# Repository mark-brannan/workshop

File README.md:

# workshop
My home workshop stuff.

Rules for the agent are in `AGENTS.md` (not here!)

Machines are in `equipment.md`

## Layout

| Path | What |
|---|---|
| `src/shop/` | Helpers: export every format at once, headless PNG render, test loader |
| `projects/<slug>/` | One part each: `README.md`, `model.py` or `model.scad`, `test_model.py`, `out/` |
| `fusion/` | Fusion 360 scripts, run inside Fusion |
| `projects/calibration/` | First real project: fit numbers for the printer and laser |
| `.github/workflows/build.yml` | Tests and builds every Python model on push |

## Setup

    ~/workshop/setup.sh     # puts `shop` on PATH; yadm bootstrap runs it

Then `shop build`, `shop doctor` (which tools this box has), `shop fusion`
(the folder to add in Fusion's Scripts panel) from any directory.

## Commands

[`RUNBOOK.md`](RUNBOOK.md) is every `shop` command by task, printing included.

    uv sync
    uv run python -m shop.build                      # every project, .py and .scad alike
    uv run python -m shop.build projects/esp32-freenove-universal-mount  # one project
    uv run pytest -q
    shop views projects/<slug>/model.scad <view>   # six labelled OpenSCAD views, montaged into out/

`.scad` models build through whatever OpenSCAD the box has (`src/shop/scad.py`);
on WSL the Windows Nightly is preferred when installed. `projects/README-ab.md` is the measured
OpenSCAD vs build123d comparison on two demo parts (since removed; see git history).

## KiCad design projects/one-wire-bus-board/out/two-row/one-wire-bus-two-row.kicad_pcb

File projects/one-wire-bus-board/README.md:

# One-wire bus board

Symphony: [`firmware/halmet/src/halmet_onewire.h`](https://github.com/mark-brannan/symphony/tree/main/firmware/halmet/src/halmet_onewire.h), [`reference/halmet_firmware.md`](https://github.com/mark-brannan/symphony/tree/main/reference/halmet_firmware.md)

Purpose: tie seven 3-pin screw terminals, each [G D V] in a row, into three nets
(GND, DATA, VCC) with no jumpers and no insulated wire. Six field terminals and a
MASTER whose cable goes to the microcontroller. Any 3-position 2.54 mm screw block, on the front edge, wire entry facing out. Pins are 2.54 mm apart inside a block and 8.2 mm pitch across blocks: the ZPWAN AM128-2.54 body is 8.1 wide by the maker's diagram (7.3-7.8 by calipers), so blocks cannot butt at 3 x 2.54 = 7.62.

Two copper layers, plated pads, no vias: G on top behind the pin row, V on top in front
of it (under the terminal body), D on the bottom between the pin row and G, so D passes under the G stubs.
Hand-built equivalent on a one-sided pad board: bare wire for G and V on the solder
side, one bare wire for D on the top face dipping through each D hole.

R1 is an optional 4.7 k pull-up spot, DATA to VCC, past MASTER: leave it empty when the master has its own.

Outputs in `out/one-row/` (the other forms each have their own folder under `out/`): `one-wire-bus-one-row.kicad_pcb` (KiCad 7 text, generated by `model.py`),
`one-wire-bus-one-row.png` (both layers), and `fab/` (below). Board 76.0 x 10.8 mm, two M3 holes 70 mm apart, each
clear of a 7 mm washer. The same pin grid works on a 2.54 mm perfboard.

Ordering, prices and OSH Park's rules: [oshpark.md](oshpark.md).

## Guessed, not measured

| Value | Now | Why |
|---|---|---|
| Pad / drill | 1.9 / 1.3 mm | commodity 2.54 mm screw block (KF2.54-3P class) |
| Body depth, pin setback | 6.5; 3.3 from the front | commodity 2.54 mm screw block; any in-stock 3P part fits |
| Track width, min clearance | DATA 0.5, GND and VCC 1.0 / 0.3 mm | fab-safe defaults; OSH Park's floor is 0.15 |
| R1 pads | 7.62 pitch, 0.8 drill | fits a 1/4 W axial resistor, body up to 6.3 x 2.5 |
| Terminal pin order | G, D, V, left to right with the wire entry facing you | owner's brief |
| Board lip past the body front | 0.5 mm | keeps copper off the edge |

Blocks sit 8.2 mm apart (`block_pitch`): clear of the 8.1 mm diagram width.

## Four forms: which one to order

The same circuit in four shapes. Each is complete: board file, Gerber zip, KiCad rule check clean against OSH Park's limits.
`model.py` builds the one-row board, `layouts.py` the other three.

| | One-row | Two-row | Ring | Pinwheel |
|---|---|---|---|---|
| Board, mm | 76.0 x 10.8 | 42.0 x 18.6 | 30.7 x 30.7 | 24.0 x 24.0 |
| Three boards at OSH Park | $6.36 | $6.07 | $7.30 | $4.46 |
| Terminal blocks | 7 x 3-position | 2 x 9-position, 1 x 3-position | 7 x 3-position | 7 x 3-position |
| Screws | 2 x M3, 7 mm washers | 4 x M2.5, corners | 4 x M3, corners | 2 x M3, 10 mm apart |
| Wires leave | one long edge | both long edges and one end | all four edges | all four edges |
| MASTER | last in the row | centred on the right end | centred on the left side | lower end of the left side |
| G D V printed where it shows once built | yes | yes | yes, inside the ring | bottom face only |
| Upload | [zip](out/one-row/fab/one-wire-bus-one-row-gerbers.zip) | [zip](out/two-row/fab/one-wire-bus-two-row-gerbers.zip) | [zip](out/ring/fab/one-wire-bus-ring-gerbers.zip) | [zip](out/pinwheel/fab/one-wire-bus-pinwheel-gerbers.zip) |
| Built, with stand-in parts | [front](out/one-row/assembled-front.png) | [front](out/two-row/assembled-front.png) | [front](out/ring/assembled-front.png) | [front](out/pinwheel/assembled-front.png) |

Prices are area times OSH Park's $5 per square inch for three boards, not a site quote.

- **One-row**: every cable comes in from one side, as on a DIN rail or along a wall. The longest board.
- **Two-row**: the narrowest board with four screws. It needs 9-position blocks, and their body depth is taken from the
  3-position part, not measured. The M2.5 pan heads beside MASTER clear its body by 0.16 mm: check with the part in hand.
- **Ring**: four M3 screws and a centred MASTER, with room in the middle for the labels and the pull-up. The largest area.
  VCC passes each corner 0.1 mm outside a 5.6 mm pan head, under solder mask: no washer wider than the head.
- **Pinwheel**: the smallest and cheapest. Two screws close together hold it, so the cables want their own strain relief.
  Once the blocks are on, the G D V letters are under them: every terminal reads G D V left to right with its wire entry facing you.

In all three compact forms R1 is the same optional 4.7 k pull-up, and every terminal, MASTER included, reads G D V left
to right from outside. On the ring and the pinwheel the pins inside a block are 2.54 mm apart and the two blocks of a side 8.2 mm apart.
Screw heads: M3 pan 5.6 mm, M2.5 pan 5.0 mm (ISO 7045).

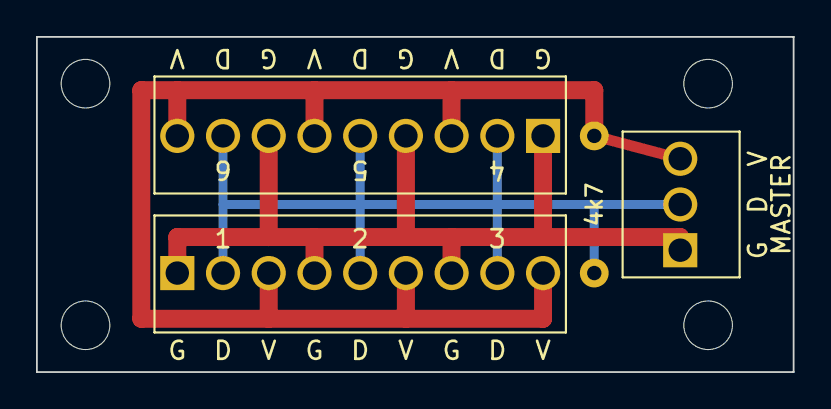
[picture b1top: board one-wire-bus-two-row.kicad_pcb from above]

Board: 2 copper layers, 42.0 x 18.6 mm, 8 parts (0 on the bottom side), 3 nets.

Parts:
H1, H2, H3, H4: MountingHole_M2.5
J1, J2: ScrewBlock_1x9_P2.54mm
J3: ScrewBlock_1x3_P2.54mm
R1: R_Axial_P7.62mm

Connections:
DATA: J1.2, J1.5, J1.8, J2.2, J2.5, J2.8, J3.2, R1.2
GND: J1.1, J1.4, J1.7, J2.1, J2.4, J2.7, J3.1
VCC: J1.3, J1.6, J1.9, J2.3, J2.6, J2.9, J3.3, R1.1

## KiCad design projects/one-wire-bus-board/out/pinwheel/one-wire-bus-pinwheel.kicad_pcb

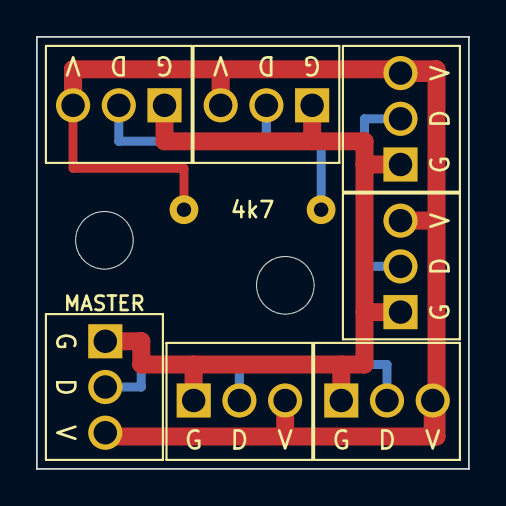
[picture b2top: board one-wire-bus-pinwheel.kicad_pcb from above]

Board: 2 copper layers, 24.0 x 24.0 mm, 10 parts (0 on the bottom side), 3 nets.

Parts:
H1, H2: MountingHole_M3
J1, J2, J3, J4, J5, J6, J7: ScrewBlock_1x3_P2.54mm
R1: R_Axial_P7.62mm

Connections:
DATA: J1.2, J2.2, J3.2, J4.2, J5.2, J6.2, J7.2, R1.2
GND: J1.1, J2.1, J3.1, J4.1, J5.1, J6.1, J7.1
VCC: J1.3, J2.3, J3.3, J4.3, J5.3, J6.3, J7.3, R1.1
